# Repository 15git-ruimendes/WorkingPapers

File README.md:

# WorkingPapers
Usefull papers for inverter and DC converter applications.

## ToUpload Folder
To upload folder serves as a repositiory for bibtex citations that have yet to be placed into notion.
The typical use case is then:
- Download citation into ToUpload.
- Run python notion API code.
- Download PDF and place PDF into the PDFs folder.

## Uploaded Folder
Uploaded folder is a form of housekeeping to mantain the already uploaded citations.

## PDFs Folder
Within this foldere all or the available PDF files should be placed.

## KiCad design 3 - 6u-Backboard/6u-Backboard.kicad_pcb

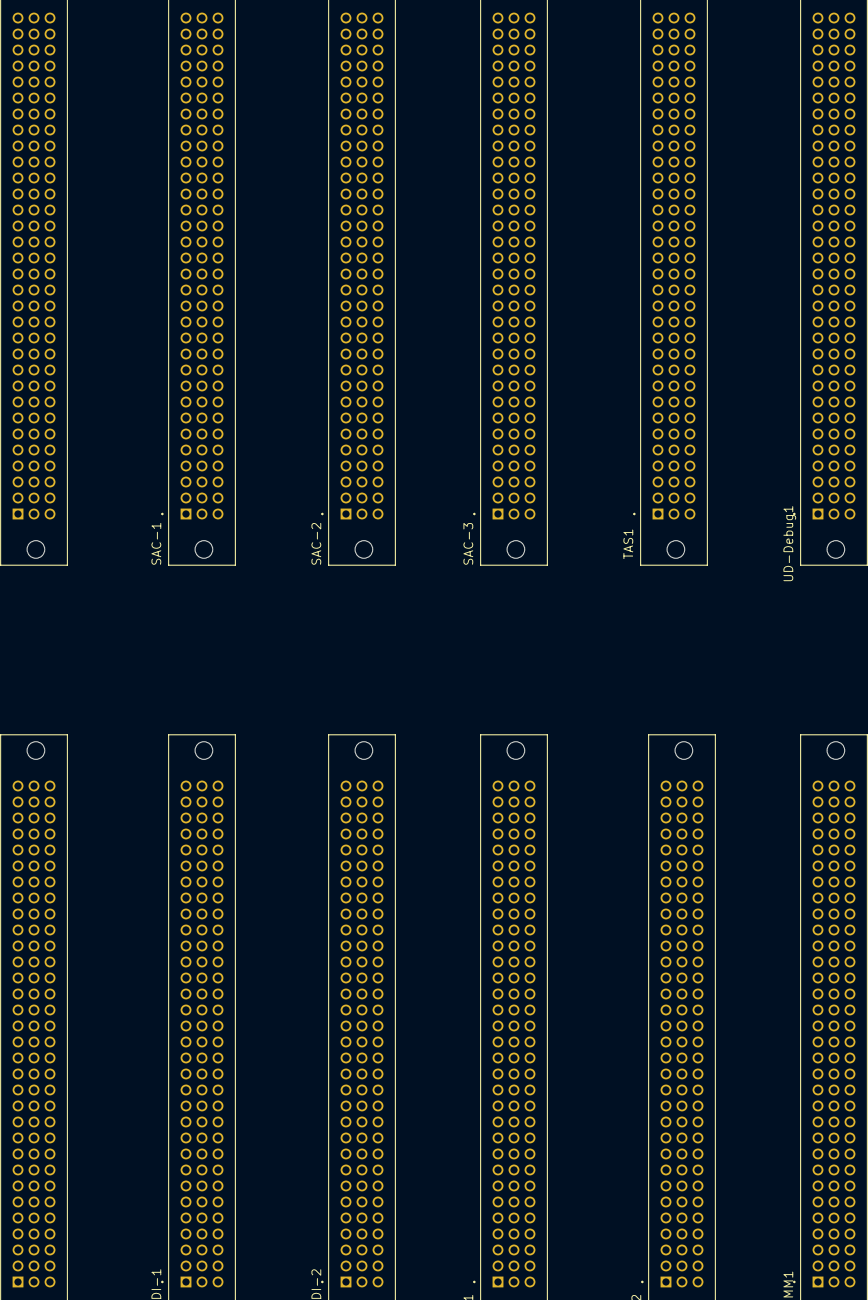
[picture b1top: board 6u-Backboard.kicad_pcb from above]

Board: 2 copper layers, 12 parts (0 on the bottom side), 40 nets, no tracks yet.

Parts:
ControlCard-Down1: 4-1393637-6; TE_4-1393637-6
ControlCard-Up1: 4-1393637-6; TE_4-1393637-6
GPRO-SDI-1, GPRO-SDI-2: 4-1393637-6; TE_4-1393637-6
IIS-1, IIS-2: 4-1393637-6; TE_4-1393637-6
LOG-COMM1: 4-1393637-6; TE_4-1393637-6
SAC-1, SAC-2, SAC-3: 4-1393637-6; TE_4-1393637-6
TAS1: 4-1393637-6; TE_4-1393637-6
UD-Debug1: 4-1393637-6; TE_4-1393637-6

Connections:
1A: SAC-1.19, SAC-1.51, SAC-1.83
1B: SAC-1.21, SAC-1.53, SAC-1.85
1C: SAC-1.23, SAC-1.55, SAC-1.87
1CH1: IIS-1.19, IIS-1.51, IIS-1.83
1CH2: IIS-1.21, IIS-1.53, IIS-1.85
1CH3: IIS-1.23, IIS-1.55, IIS-1.87
1CH4: IIS-1.25, IIS-1.57, IIS-1.89
1CH5: IIS-1.27, IIS-1.59, IIS-1.91
1CH6: IIS-1.29, IIS-1.61, IIS-1.93
1D: SAC-1.25, SAC-1.57, SAC-1.89
1E: SAC-1.27, SAC-1.59, SAC-1.91
1F: SAC-1.29, SAC-1.61, SAC-1.93
2A: SAC-2.19, SAC-2.51, SAC-2.83
2B: SAC-2.21, SAC-2.53, SAC-2.85
2C: SAC-2.23, SAC-2.55, SAC-2.87
2CH1: IIS-2.19, IIS-2.51, IIS-2.83
2CH2: IIS-2.21, IIS-2.53, IIS-2.85
2CH3: IIS-2.23, IIS-2.55, IIS-2.87
2CH4: IIS-2.25, IIS-2.57, IIS-2.89
2CH5: IIS-2.27, IIS-2.59, IIS-2.91
2CH6: IIS-2.29, IIS-2.61, IIS-2.93
2D: SAC-2.25, SAC-2.57, SAC-2.89
2E: SAC-2.27, SAC-2.59, SAC-2.91
2F: SAC-2.29, SAC-2.61, SAC-2.93
3A: SAC-3.19, SAC-3.51, SAC-3.83
3B: SAC-3.21, SAC-3.53, SAC-3.85
3C: SAC-3.23, SAC-3.55, SAC-3.87
3D: SAC-3.25, SAC-3.57, SAC-3.89
3E: SAC-3.27, SAC-3.59, SAC-3.91
3F: SAC-3.29, SAC-3.61, SAC-3.93
12V: IIS-1.9, IIS-1.41, IIS-1.73, IIS-2.9, IIS-2.41, IIS-2.73, SAC-1.9, SAC-1.41, SAC-1.73, SAC-2.9, SAC-2.41, SAC-2.73, SAC-3.9, SAC-3.41, SAC-3.73
15V: IIS-1.5, IIS-1.37, IIS-1.69, IIS-2.5, IIS-2.37, IIS-2.69, SAC-1.5, SAC-1.37, SAC-1.69, SAC-2.5, SAC-2.37, SAC-2.69, SAC-3.5, SAC-3.37, SAC-3.69
24V: IIS-1.1, IIS-1.33, IIS-1.65, IIS-2.1, IIS-2.33, IIS-2.65, SAC-1.1, SAC-1.33, SAC-1.65, SAC-2.1, SAC-2.33, SAC-2.65, SAC-3.1, SAC-3.33, SAC-3.65
-12V: IIS-1.11, IIS-1.43, IIS-1.75, IIS-2.11, IIS-2.43, IIS-2.75, SAC-1.11, SAC-1.43, SAC-1.75, SAC-2.11, SAC-2.43, SAC-2.75, SAC-3.11, SAC-3.43, SAC-3.75
-15V: IIS-1.7, IIS-1.39, IIS-1.71, IIS-2.7, IIS-2.39, IIS-2.71, SAC-1.7, SAC-1.39, SAC-1.71, SAC-2.7, SAC-2.39, SAC-2.71, SAC-3.7, SAC-3.39, SAC-3.71
-24V: IIS-1.3, IIS-1.35, IIS-1.67, IIS-2.3, IIS-2.35, IIS-2.67, SAC-1.3, SAC-1.35, SAC-1.67, SAC-2.3, SAC-2.35, SAC-2.67, SAC-3.3, SAC-3.35, SAC-3.67
CAN-High: IIS-1.13, IIS-1.45, IIS-1.77, IIS-2.13, IIS-2.45, IIS-2.77, SAC-1.13, SAC-1.45, SAC-1.77, SAC-2.13, SAC-2.45, SAC-2.77, SAC-3.13, SAC-3.45, SAC-3.77
CAN-Low: IIS-1.15, IIS-1.47, IIS-1.79, IIS-2.15, IIS-2.47, IIS-2.79, SAC-1.15, SAC-1.47, SAC-1.79, SAC-2.15, SAC-2.47, SAC-2.79, SAC-3.15, SAC-3.47, SAC-3.79
GND: IIS-1.2, IIS-1.4, IIS-1.6, IIS-1.8, IIS-1.10, IIS-1.12, IIS-1.14, IIS-1.16, IIS-1.18, IIS-1.20, IIS-1.22, IIS-1.24, IIS-1.26, IIS-1.28, IIS-1.30, IIS-1.31, IIS-1.32, IIS-1.34, IIS-1.36, IIS-1.38, IIS-1.40, IIS-1.42, IIS-1.44, IIS-1.46, IIS-1.48, IIS-1.50, IIS-1.52, IIS-1.54, IIS-1.56, IIS-1.58, IIS-1.60, IIS-1.62, IIS-1.63, IIS-1.64, IIS-1.66, IIS-1.68, IIS-1.70, IIS-1.72, IIS-1.74, IIS-1.76, IIS-1.78, IIS-1.80, IIS-1.82, IIS-1.84, IIS-1.86, IIS-1.88, IIS-1.90, IIS-1.92, IIS-1.94, IIS-1.95, IIS-1.96, IIS-2.2, IIS-2.4, IIS-2.6, IIS-2.8, IIS-2.10, IIS-2.12, IIS-2.14, IIS-2.16, IIS-2.18, IIS-2.20, IIS-2.22, IIS-2.24, IIS-2.26, IIS-2.28, IIS-2.30, IIS-2.31, IIS-2.32, IIS-2.34, IIS-2.36, IIS-2.38, IIS-2.40, IIS-2.42, IIS-2.44, IIS-2.46, IIS-2.48, IIS-2.50, IIS-2.52, IIS-2.54, IIS-2.56, IIS-2.58, IIS-2.60, IIS-2.62, IIS-2.63, IIS-2.64, IIS-2.66, IIS-2.68, IIS-2.70, IIS-2.72, IIS-2.74, IIS-2.76, IIS-2.78, IIS-2.80, IIS-2.82, IIS-2.84, IIS-2.86, IIS-2.88, IIS-2.90, IIS-2.92, IIS-2.94, IIS-2.95, IIS-2.96, SAC-1.2, SAC-1.4, SAC-1.6, SAC-1.8, SAC-1.10, SAC-1.12, SAC-1.14, SAC-1.16, SAC-1.18, SAC-1.20, SAC-1.22, SAC-1.24, SAC-1.26, SAC-1.28, SAC-1.30, SAC-1.31, SAC-1.32, SAC-1.34, SAC-1.36, SAC-1.38, SAC-1.40, SAC-1.42, SAC-1.44, SAC-1.46, SAC-1.48, SAC-1.50, SAC-1.52, SAC-1.54, SAC-1.56, SAC-1.58, SAC-1.60, SAC-1.62, SAC-1.63, SAC-1.64, SAC-1.66, SAC-1.68, SAC-1.70, SAC-1.72, SAC-1.74, SAC-1.76, SAC-1.78, SAC-1.80, SAC-1.82, SAC-1.84, SAC-1.86, SAC-1.88, SAC-1.90, SAC-1.92, SAC-1.94, SAC-1.95, SAC-1.96, SAC-2.2, SAC-2.4, SAC-2.6, SAC-2.8, SAC-2.10, SAC-2.12, SAC-2.14, SAC-2.16, SAC-2.18, SAC-2.20, SAC-2.22, SAC-2.24, SAC-2.26, SAC-2.28, SAC-2.30, SAC-2.31, SAC-2.32, SAC-2.34, SAC-2.36, SAC-2.38, SAC-2.40, SAC-2.42, SAC-2.44, SAC-2.46, SAC-2.48, SAC-2.50, SAC-2.52, SAC-2.54, SAC-2.56, SAC-2.58, SAC-2.60, SAC-2.62, SAC-2.63, SAC-2.64, SAC-2.66, SAC-2.68, SAC-2.70, SAC-2.72, SAC-2.74, SAC-2.76, SAC-2.78, SAC-2.80, SAC-2.82, SAC-2.84, SAC-2.86, SAC-2.88, SAC-2.90, SAC-2.92, SAC-2.94, SAC-2.95, SAC-2.96, SAC-3.2, SAC-3.4, SAC-3.6, SAC-3.8, SAC-3.10, SAC-3.12, SAC-3.14, SAC-3.16, SAC-3.18, SAC-3.20, SAC-3.22, SAC-3.24, SAC-3.26, SAC-3.28, SAC-3.30, SAC-3.31, SAC-3.32, SAC-3.34, SAC-3.36, SAC-3.38, SAC-3.40, SAC-3.42, SAC-3.44, SAC-3.46, SAC-3.48, SAC-3.50, SAC-3.52, SAC-3.54, SAC-3.56, SAC-3.58, SAC-3.60, SAC-3.62, SAC-3.63, SAC-3.64, SAC-3.66, SAC-3.68, SAC-3.70, SAC-3.72, SAC-3.74, SAC-3.76, SAC-3.78, SAC-3.80, SAC-3.82, SAC-3.84, SAC-3.86, SAC-3.88, SAC-3.90, SAC-3.92, SAC-3.94, SAC-3.95, SAC-3.96
SafetyLoop: IIS-1.17, IIS-1.49, IIS-1.81, IIS-2.17, IIS-2.49, IIS-2.81, SAC-1.17, SAC-1.49, SAC-1.81, SAC-2.17, SAC-2.49, SAC-2.81, SAC-3.17, SAC-3.49, SAC-3.81

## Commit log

2022-10-12 Papers
2022-10-17 ORganized
2022-10-17 Moew organized
2022-10-17 topxuxão megalaife #vidaboa
2022-10-25 MoreDAB
2022-10-25 More DAB papers
2022-11-14 More stuff
2022-11-15 Another Commit
2022-11-15 clean
2022-11-20 Supervisor code updated and changed priorities
2022-11-24 6U backplane in kicad for pin assignment
2022-11-28 Possible configurator and monitor solution
2022-12-18 More papers to read
2022-12-18 More papers
2022-12-20 More Stff
2022-12-20 CAN test prob working
2022-12-20 Manage
2022-12-26 STM32 Tests
2022-12-26 Teste
2023-01-01 SD Card Tests
2023-01-02 ADC and USART tests
2023-01-08 Frontend done
2023-01-29 Updated TAS code and code snippets for rpi can tester.
2023-01-29 Updates to TAS code and python code for CAN RPI
2023-01-30 CAN Tester
